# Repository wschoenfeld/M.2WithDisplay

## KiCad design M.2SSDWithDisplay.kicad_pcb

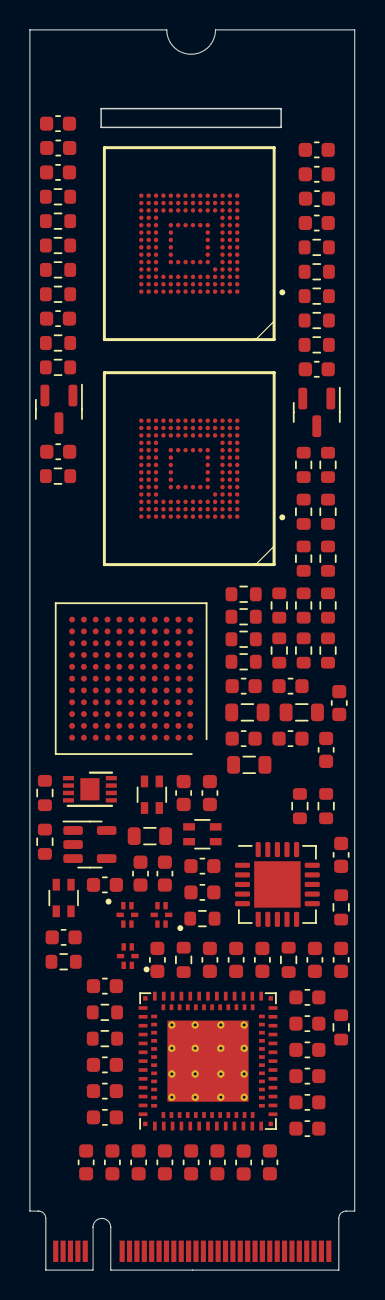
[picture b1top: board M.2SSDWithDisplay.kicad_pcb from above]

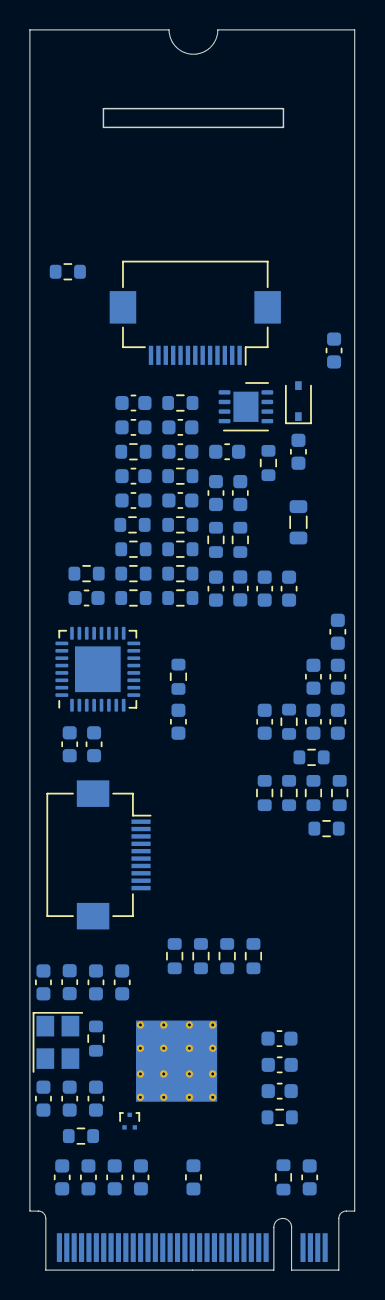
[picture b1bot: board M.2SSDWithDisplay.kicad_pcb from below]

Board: 6 copper layers, 22.0 x 84.0 mm, 192 parts (82 on the bottom side), 130 nets, no tracks yet.

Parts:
C1, C2, C3, C9, C10, C11, C12, C13, C14, C15, C16, C17, C18, C19, C20, C21, C22, C35, C36, C37, C38, C39, C40, C41, C46, C47, C48, C49, C53, C57, C59, C61, C63, C64, C65, C66, C67, C68, C73, C78, C80, C82, C87, C89: 0.1uF; C_0603_1608Metric
C4, C6, C7, C75, C76, C77, C84, C85, C86: 1uF; C_0603_1608Metric
C5, C74, C83: 4.7uF; C_0603_1608Metric
C8, C25, C34, C45, C58, C60, C62: 22uF; C_0603_1608Metric
C23, C24, C54, C55: 10uF; C_0603_1608Metric
C26, C27, C28, C29, C30, C31, C32, C33, C42, C43, C44, C56, C69, C70, C71, C72: 10nF; C_0603_1608Metric
C50, C51: 18pF; C_0603_1608Metric
C52, C79, C81, C88, C90: 2.2uF; C_0603_1608Metric
D1: NSR0340HT1G; D_SOD-323
FB1: 220 @ 100MHz; L_0603_1608Metric
J1: Conn_01x10; Hirose_FH12-10S-0.5SH_1x10-1MP_P0.50mm_Horizontal
J2: Conn_01x13; Hirose_FH12-13S-0.5SH_1x13-1MP_P0.50mm_Horizontal
J3: Bus_M.2_Socket_M; NGFF_M
L1: 4.7uH; L_0805_2012Metric
L2, L3, L4: LCFE121002; FIL_LCFE121002A900TG
L5, L6, L7, L8: 600 @ 2A; L_0805_2012Metric
R1, R5, R10, R11, R12, R19, R20, R23, R29, R30, R31, R32, R45, R58, R59, R60, R61, R62, R63, R64, R65, R66, R67, R68, R69, R70, R71, R72, R73: 0; R_0603_1608Metric
R2, R8, R15, R16, R17, R26, R27, R28, R33, R34, R35, R36, R37, R38, R39, R40, R41, R46, R47, R48, R49, R50, R51, R52, R53, R54: 10K; R_0603_1608Metric
R3: 24K; R_0603_1608Metric
R4: 8; R_0603_1608Metric
R6, R14: 4.7K; R_0603_1608Metric
R7: 1.87K; R_0603_1608Metric
R9: 4.99K; R_0603_1608Metric
R13: 1M; R_0603_1608Metric
R18: 9.09K; R_0603_1608Metric
R21: 6.04K; R_0603_1608Metric
R22: 200; R_0603_1608Metric
R24, R25: 2K; R_0603_1608Metric
R42, R44, R55, R57: 50K; R_0603_1608Metric
R43, R56: 22; R_0603_1608Metric
RN1: R_Pack02; R_Array_Convex_2x0603
RN2, RN3: 0; R_Array_Convex_2x0603
U1: ATmega8U2-M; QFN-32-1EP_5x5mm_P0.5mm_EP3.1x3.1mm
U2: TUSB7320; Texas_S-PWQFN-N100_EP5.5x5.5mm_ThermalVias
U3: STLD40DPUR; DFN-8-1EP_3x3mm_P0.65mm_EP1.7x2.05mm
U4: ﻿CYUSB3025; TFBGA-121_10x10mm_Layout11x11_P0.8mm
U5, U11: MTFC32GAZAQHD-AAT; BGA153N50P14X14_1150X1300X100
U6: TPS74401_VQFN; Texas_S-PVQFN-N20_EP3.15x3.15mm
U7: TPD2EUSB30; Texas_DRT-3
U8: TLV75512PDBV; SOT-23-5
U9: 24CS256; DFN-8-1EP_3x2mm_P0.5mm_EP1.3x1.5mm
U10, U12: APE8865N-18-HF-3; SOT-23
Y1: 48MHz; Crystal_SMD_3225-4Pin_3.2x2.5mm

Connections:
/EMMC1/+3.3V: C23.1, C35.1, C36.1, C37.1, FB1.1, J3.2 (3.3V), J3.4 (3.3V), J3.12 (3.3V), J3.14 (3.3V), J3.16 (3.3V), J3.18 (3.3V), J3.70 (3.3V), J3.72 (3.3V), J3.74 (3.3V), R1.1, R5.1, R10.1, R23.1, R32.1, R45.1
/EMMC1/CLK: R43.2, U4.G2 (GPIO[42]/S0_CLK)
/EMMC1/CMD: R41.2, U4.F4 (GPIO[41]/S0_CMD), U5.M5 (CMD)
/EMMC1/EMMC_D0: R40.2, R58.2, U5.A3 (DAT0)
/EMMC1/EMMC_D0R: R58.1, U4.K2 (GPIO[33]/S0_D0)
/EMMC1/EMMC_D1: R39.2, R59.2, U5.A4 (DAT1)
/EMMC1/EMMC_D1R: R59.1, U4.J4 (GPIO[34]/S0_D1)
/EMMC1/EMMC_D2: R38.2, R60.2, U5.A5 (DAT2)
/EMMC1/EMMC_D2R: R60.1, U4.K1 (GPIO[35]/S0_D2)
/EMMC1/EMMC_D3: R37.2, R61.2, U5.B1 (NC1), U5.B2 (DAT3)
/EMMC1/EMMC_D3R: R61.1, U4.J2 (GPIO[36]/S0_D3)
/EMMC1/EMMC_D4: R36.2, R62.2, U5.A2 (NC1), U5.B3 (DAT4)
/EMMC1/EMMC_D4R: R62.1, U4.J3 (GPIO[37]/S0_D4)
/EMMC1/EMMC_D5: R35.2, R63.2, U5.B4 (DAT5), U5.C3 (NC2), U5.D3 (NC3)
/EMMC1/EMMC_D5R: R63.1, U4.J1 (GPIO[38]/S0_D5)
/EMMC1/EMMC_D6: R34.2, R64.2, U5.A9 (NC1), U5.B5 (DAT6), U5.B8 (NC1), U5.C5 (NC2), U5.C7 (NC2)
/EMMC1/EMMC_D6R: R64.1, U4.H2 (GPIO[39]/S0_D6)
/EMMC1/EMMC_D7: R33.2, R65.2, U5.A8 (NC1), U5.B6 (DAT7), U5.B7 (NC1)
/EMMC1/EMMC_D7R: R65.1, U4.H3 (GPIO[40]/S0_D7)
/EMMC1/RST: R42.2, U4.F2 (GPIO[45]/S0_RST), U5.K5 (RST_N)
/EMMC2/CLK: R56.2, U4.D2 (GPIO[51]/S1_CLK)
/EMMC2/CMD: R54.2, U4.D1 (GPIO[50]/S1_CMD), U11.M5 (CMD)
/EMMC2/EMMC_D0: R53.2, R66.2, U11.A3 (DAT0)
/EMMC2/EMMC_D0R: R66.1, U4.F5 (GPIO[46]/S1_D0)
/EMMC2/EMMC_D1: R52.2, R67.2, U11.A4 (DAT1)
/EMMC2/EMMC_D1R: R67.1, U4.E1 (GPIO[47]/S1_D1)
/EMMC2/EMMC_D2: R51.2, R68.2, U11.A5 (DAT2)
/EMMC2/EMMC_D2R: R68.1, U4.E5 (GPIO[48]/S1_D2)
/EMMC2/EMMC_D3: R50.2, R69.2, U11.B1 (NC1), U11.B2 (DAT3)
/EMMC2/EMMC_D3R: R69.1, U4.E4 (GPIO[49]/S1_D3)
/EMMC2/EMMC_D4: R49.2, R70.2, U11.A2 (NC1), U11.B3 (DAT4)
/EMMC2/EMMC_D4R: R70.1, U4.D4 (GPIO[53]/S1_D4)
/EMMC2/EMMC_D5: R48.2, R71.2, U11.B4 (DAT5), U11.C3 (NC2), U11.D3 (NC3)
/EMMC2/EMMC_D5R: R71.1, U4.C1 (GPIO[54]/S1_D5)
/EMMC2/EMMC_D6: R47.2, R72.2, U11.A9 (NC1), U11.B5 (DAT6), U11.B8 (NC1), U11.C5 (NC2), U11.C7 (NC2)
/EMMC2/EMMC_D6R: R72.1, U4.C2 (GPIO[55]/S1_D6)
/EMMC2/EMMC_D7: R46.2, R73.2, U11.A8 (NC1), U11.B6 (DAT7), U11.B7 (NC1)
/EMMC2/EMMC_D7R: R73.1, U4.D5 (GPIO[56]/S1_D7)
/EMMC2/RST: R55.2, U4.C4 (GPIO[57]/S1_RST), U11.K5 (RST_N)
/M.2 Edge & Bridge/M2_RX+: C48.1, J3.43 (PERp0/SATA-B-)
/M.2 Edge & Bridge/M2_RX-: C49.1, J3.41 (PERn0/SATA-B+)
/M.2 Edge & Bridge/M2_TX+: J3.49 (PETp0/SATA-A+), R11.1
/M.2 Edge & Bridge/M2_TX-: J3.47 (PETn0/SATA-A-), R12.1
/M.2 Edge & Bridge/U2_1.1V: C8.1, C9.1, C10.1, C11.1, C12.1, C13.1, C14.1, C15.1, C16.1, C17.1, C18.1, C19.1, C20.1, C21.1, C25.1, C27.1, C28.1, C29.1, C30.1, C31.1, C32.1, C33.1, R7.1, U2.A1 (VDD11), U2.A4 (VDD11), U2.A6 (VDD11), U2.A9 (VDD11), U2.A12 (VDD11), U2.A16 (VDD11), U2.A28 (VDD11), U2.A31 (VDD11), U2.A33 (VDD11), U2.A38 (VDD11), U2.A50 (VDD11), U2.B1 (VDD11), U2.B17 (VDD11), U2.B19 (VDD11), U2.B24 (VDD11), U2.B37 (VDD11), U2.B40 (VDD11), U2.B42 (VDD11), U2.B44 (VDD11), U6.1 (OUT), U6.18 (OUT), U6.19 (OUT), U6.20 (OUT)
/M.2 Edge & Bridge/U2_3.3V: C34.1, R10.2, R15.1, R16.1, R17.1, U2.A3 (VDD33), U2.A34 (VDD33), U2.A39 (VDD33), U2.A47 (VDD33), U2.A51 (VDD33)
/M.2 Edge & Bridge/U2_3.3VA: C38.1, C39.1, C40.1, C41.1, C42.1, C43.1, C44.1, C45.1, FB1.2, U2.A19 (VDDA_3P3), U2.A21 (VDDA_3P3), U2.A25 (VDDA_3P3), U2.A44 (VDDA_3P3), U2.B4 (VDDA_3P3), U2.B11 (VDDA_3P3), U2.B22 (VDDA_3P3), U2.B26 (VDDA_3P3)
/M.2 Edge & Bridge/U2_RST: C22.1, R8.1, U2.A15 (GRST#), U6.9 (PG)
/M.2 Edge & Bridge/U2_RX+: R11.2, U2.B39 (PCIE_RXP)
/M.2 Edge & Bridge/U2_RX-: R12.2, U2.A42 (PCIE_RXN)
/M.2 Edge & Bridge/U2_TX+: C48.2, U2.B38 (PCIE_TXP)
/M.2 Edge & Bridge/U2_TX-: C49.2, U2.A41 (PCIE_TXN)
/M.2 Edge & Bridge/USB1_D+: RN1.2 (R2.1), U4.A9 (DP)
/M.2 Edge & Bridge/USB1_D-: RN1.1 (R1.1), U4.A10 (DM)
/M.2 Edge & Bridge/USB1_RX+: RN3.2 (R2.1), U4.A5 (SSTXP)
/M.2 Edge & Bridge/USB1_RX-: RN3.1 (R1.1), U4.A6 (SSTXM)
/M.2 Edge & Bridge/USB1_TX+: RN2.2 (R2.1), U4.A4 (SSRXP)
/M.2 Edge & Bridge/USB1_TX-: RN2.1 (R1.1), U4.A3 (SSRXM)
/Microntroller & Display/DISP_3V3: C1.1, C2.1, C3.1, C4.1, J1.5, J1.9, J2.10, L1.1, R1.2, R2.1, U1.4 (VCC), U1.31 (UVCC), U1.32 (AVCC), U3.1 (VI)
/Microntroller & Display/DISP_DC: J2.5, U1.21 (PB7)
/Microntroller & Display/DISP_MISO: J1.1, U1.17 (MISO/PB3)
/Microntroller & Display/DISP_MOSI: J1.2, J2.3, U1.16 (MOSI/PB2)
/Microntroller & Display/DISP_RST: J1.4, J2.6, R2.2, U1.24 (PC1/~RESET)
/Microntroller & Display/DISP_SCK: J1.3, J2.4, U1.15 (SCLK/PB1)
/Microntroller & Display/MCU_USB_D+: J1.7, L4.3, U1.29 (D+)
/Microntroller & Display/MCU_USB_D-: J1.8, L4.4, U1.30 (D-)
/Storage Controller/U4_AVDD: C52.1, C53.1, L5.2, U4.A7 (AVDD)
/Storage Controller/U4_CVDDQ: C56.1, C57.1, L6.2, U4.B6 (CVDDQ)
/Storage Controller/U4_RXVDD: C58.1, C59.1, L7.2, U4.A2 (U3RXVDDQ)
/Storage Controller/U4_TXVDD: C60.1, C61.1, L8.2, U4.B5 (U3TXVDDQ)
GND: C1.2, C2.2, C3.2, C4.2, C5.2, C6.2, C7.2, C8.2, C9.2, C10.2, C11.2, C12.2, C13.2, C14.2, C15.2, C16.2, C17.2, C18.2, C19.2, C20.2, C21.2, C22.2, C23.2, C24.2, C25.2, C26.2, C27.2, C28.2, C29.2, C30.2, C31.2, C32.2, C33.2, C34.2, C35.2, C36.2, C37.2, C38.2, C39.2, C40.2, C41.2, C42.2, C43.2, C44.2, C45.2, C52.2, C53.2, C54.2, C55.2, C56.2, C57.2, C58.2, C59.2, C60.2, C61.2, C62.2, C63.2, C64.2, C65.2, C66.2, C67.2, C68.2, C69.2, C70.2, C71.2, C72.2, C73.2, C74.2, C75.2, C76.2, C77.2, C78.2, C79.2, C80.2, C81.2, C82.2, C83.2, C84.2, C85.2, C86.2, C87.2, C88.2, C89.2, C90.2, J1.6, J1.10, J2.7, J2.8, J2.13, J3.1 (GND), J3.3 (GND), J3.9 (GND), J3.15 (GND), J3.21 (GND), J3.27 (GND), J3.33 (GND), J3.39 (GND), J3.45 (GND), J3.51 (GND), J3.57 (GND), J3.71 (GND), J3.73 (GND), J3.75 (GND), R3.2, R4.2, R9.2, R14.2, R19.2, R20.2, R21.2, R22.2, R29.2, R30.2, R31.2, R44.2, R57.2, U1.3 (GND), U1.28 (UGND), U1.33 (GND), U2.A2 (SDA), U2.A53 (VSS_EP), U2.B2 (SCL), U2.B20 (VSS), U2.B32 (JTAG_RST#), U2.C1 (VSS), U2.C2 (VSS), U2.C3 (VSS), U2.C4 (VSS), U3.3 (GND), U3.9 (PGND), U4.A1 (U3VSSQ), U4.A8 (VSS[14]), U4.B7 (AVSS), U4.B8 (VSS[14]), U4.B9 (VSS[14]), U4.D8 (VSS[14]), U4.E2 (VSS[14]), U4.G1 (VSS[14]), U4.G11 (VSS[14]), U4.K3 (VSS[14]), U4.K4 (VSS[14]), U4.L1 (VSS[14]), U4.L2 (VSS[14]), U4.L3 (VSS[14]), U4.L6 (VSS[14]), U4.L11 (VSS[14]), U5.A6 (VSS), U5.C4 (VSSQ), U5.E7 (VSS), U5.G5 (VSS), U5.H10 (VSS), U5.J5 (VSS), U5.K8 (VSS), U5.N2 (VSSQ), U5.N5 (VSSQ), U5.P4 (VSSQ), U5.P6 (VSSQ), U6.12 (GND), U6.21 (EP), U7.3 (GND), U8.2 (GND), U9.4 (GND), U9.7 (WP), U10.1 (GND), U11.A6 (VSS), U11.C4 (VSSQ), U11.E7 (VSS), U11.G5 (VSS), U11.H10 (VSS), U11.J5 (VSS), U11.K8 (VSS), U11.N2 (VSSQ), U11.N5 (VSSQ), U11.P4 (VSSQ), U11.P6 (VSSQ), U12.1 (GND)
unnamed: C5.1, C7.1, D1.1 (K), J2.12, U3.6 (VO)
unnamed: C6.1, U1.27 (UCAP)
unnamed: C24.1, R5.2, R6.1, R8.2, U6.5 (IN), U6.6 (IN), U6.7 (IN), U6.8 (IN), U6.10 (BIAS)
unnamed: C26.1, R6.2, U6.11 (EN)
unnamed: C46.1, L3.3
unnamed: C46.2, RN2.3 (R2.2)
unnamed: C47.1, L3.4
unnamed: C47.2, RN2.4 (R1.2)
unnamed: C50.1, R13.1, U2.A23 (XI), Y1.1
unnamed: C50.2, C51.2, U2.B21 (VSS_OSC)
unnamed: C51.1, R13.2, U2.A22 (XO), Y1.3
unnamed: C54.1, R23.2, U8.1 (IN), U8.3 (EN)
unnamed: C55.1, C62.1, C63.1, C64.1, C65.1, C66.1, C67.1, C68.1, C69.1, C70.1, C71.1, C72.1, L5.1, L6.1, L7.1, L8.1, U4.B10 (VDD[8]), U4.C3 (VDD[8]), U4.E9 (VDD[8]), U4.F11 (VDD[8]), U4.H1 (VDD[8]), U4.J11 (VDD[8]), U4.L5 (VDD[8]), U4.L7 (VDD[8]), U8.5 (OUT)
unnamed: C73.1, C74.1, C75.1, R32.2, U5.E6 (VCC), U5.F5 (VCC), U5.J10 (VCC), U5.K9 (VCC), U10.3 (VI)
unnamed: C76.1, C77.1, C78.1, C79.1, R33.1, R34.1, R35.1, R36.1, R37.1, R38.1, R39.1, R40.1, R41.1, R42.1, U5.C6 (VCCQ), U5.M4 (VCCQ), U5.N4 (VCCQ), U5.P3 (VCCQ), U5.P5 (VCCQ), U10.2 (VO)
unnamed: C80.1, C81.1, U5.C2 (VDDIM)
unnamed: C82.1, C83.1, C84.1, R45.2, U11.E6 (VCC), U11.F5 (VCC), U11.J10 (VCC), U11.K9 (VCC), U12.3 (VI)
unnamed: C85.1, C86.1, C87.1, C88.1, R46.1, R47.1, R48.1, R49.1, R50.1, R51.1, R52.1, R53.1, R54.1, R55.1, U11.C6 (VCCQ), U11.M4 (VCCQ), U11.N4 (VCCQ), U11.P3 (VCCQ), U11.P5 (VCCQ), U12.2 (VO)
unnamed: C89.1, C90.1, U11.C2 (VDDIM)
unnamed: D1.2 (A), L1.2, U3.8 (SW)
unnamed: J2.11, R4.1, U3.4 (FB)
unnamed: J3.50 (~PERST), U2.A40 (PERST#)
unnamed: J3.52 (~CLKREQ), U2.B36 (CLKREQ#)
unnamed: J3.53 (REFCLKn), U2.B41 (PCIE_REFCLKN)
unnamed: J3.54 (~PEWAKE), U2.B35 (WAKE#)
unnamed: J3.55 (REFCLKp), U2.A45 (PCIE_REFCLKP)
unnamed: L2.1, U2.B18 (USB_DM_DN1)
unnamed: L2.2, U2.A20 (USB_DP_DN1)
unnamed: L2.3, RN1.3 (R2.2)
unnamed: L2.4, RN1.4 (R1.2)
unnamed: L3.1, U2.B15 (USB_SSTXN_DN1)
unnamed: L3.2, U2.A17 (USB_SSTXP_DN1)
unnamed: L4.1, U2.A13 (USB_DM_DN2)
unnamed: L4.2, U2.B12 (USB_DP_DN2)
unnamed: R3.1, U3.2 (RSET)
unnamed: R7.2, R9.1, U6.16 (FB)
unnamed: R14.1, U2.B14 (FREQSEL)
unnamed: R15.2, U2.A36 (OVERCUR1#)
unnamed: R16.2, U2.A37 (OVERCUR2#)
unnamed: R17.2, U2.A52 (AUX_DET)
unnamed: R18.1, U2.A24 (R1EXT)
unnamed: R18.2, U2.B23 (R1EXTRTN)
unnamed: R19.1, U2.B34 (PWRON2#)
unnamed: R20.1, U2.B33 (PWRON1#)
unnamed: R21.1, U4.C8 (R_USB2)
unnamed: R22.1, U4.B3 (R_USB3)
unnamed: R24.1, R25.1, R26.1, R27.1, R28.1, U9.8 (VCC)
unnamed: R24.2, U4.D10 (I2C_GPIO[59]/SDA), U9.5 (SDA)
unnamed: R25.2, U4.D9 (I2C_GPIO[58]/SCL), U9.6 (SCL)
unnamed: R26.2, R29.1, U9.3 (A2)
unnamed: R27.2, R30.1, U9.2 (A1)
unnamed: R28.2, R31.1, U9.1 (A0)
unnamed: R43.1, U5.M6 (CLK)
unnamed: R44.1, U5.H5 (DS)
unnamed: R56.1, U11.M6 (CLK)
unnamed: R57.1, U11.H5 (DS)
unnamed: RN3.3 (R2.2), U2.A18 (USB_SSRXP_DN1), U7.1 (D+)
unnamed: RN3.4 (R1.2), U2.B16 (USB_SSRXN_DN1), U7.2 (D-)
unnamed: U1.5 (PC2), U3.7 (EN)
unnamed: U4.H11 (S2VDDQ[2]), U4.L9 (S2VDDQ[2])

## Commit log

2023-08-11 AddedFiles
